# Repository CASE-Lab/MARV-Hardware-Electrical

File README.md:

# MARV-Hardware-Electrical
Contains the electrical design files fo the MARV system. These includes the PCBs and system wiring diagram and specific wire function diagram. Some of the PCB projects includes a component library, otherwise the CASE-Association case-eagle-libraries have been used, found here: https://github.com/CASE-Association/case-eagle-libraries.git

This project uses both Eagle and KiCad ECAD programs. This is shown by folder names.

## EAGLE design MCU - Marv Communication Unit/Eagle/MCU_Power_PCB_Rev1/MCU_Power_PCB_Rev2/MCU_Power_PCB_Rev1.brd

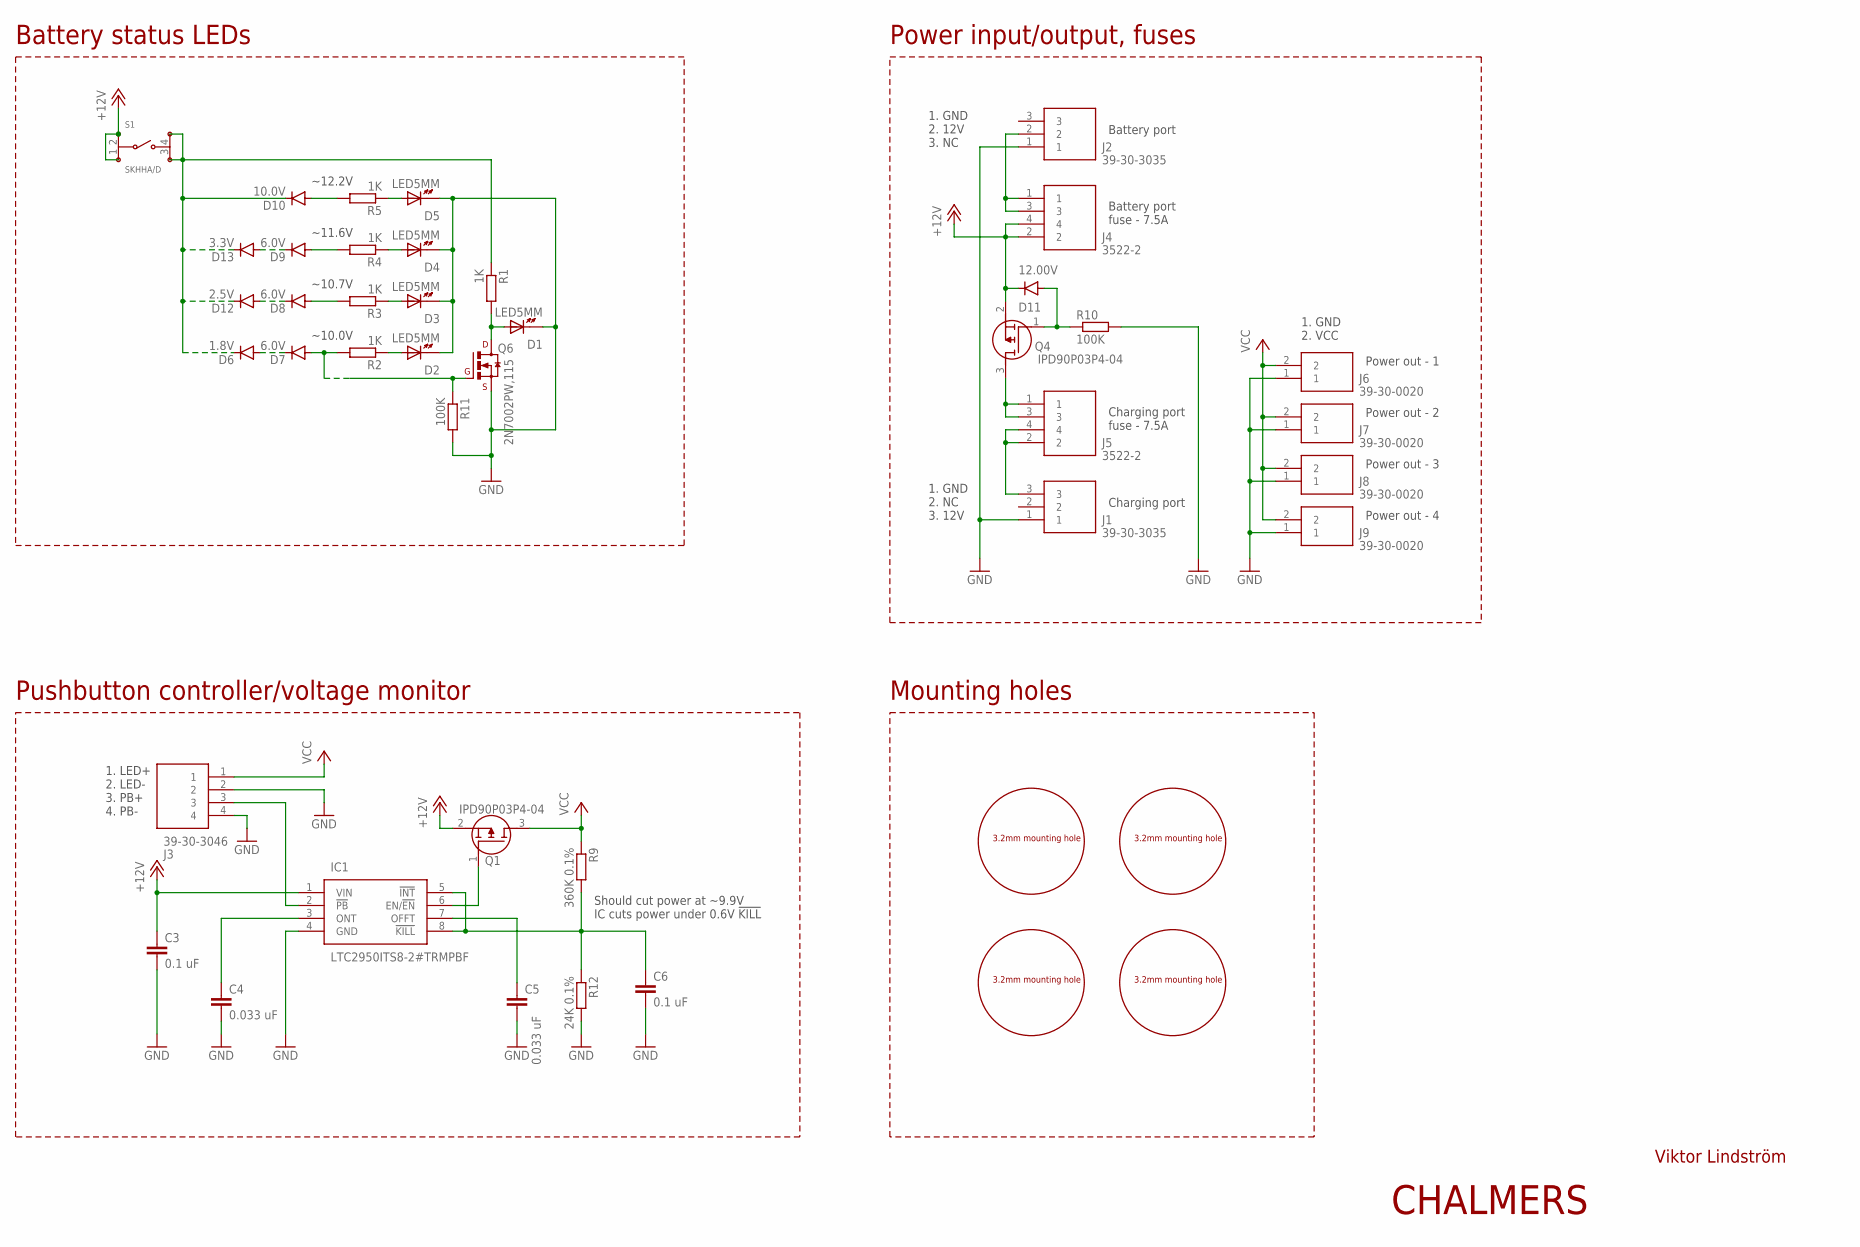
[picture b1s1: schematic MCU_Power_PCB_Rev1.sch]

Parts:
C3, C6: 0.1 uF; C0603
C4, C5: 0.033 uF; C0603
D1, D2, D3, D4, D5: LED5MM
D6: 1.8V; SOD-123_MINI-SMA
D7, D8, D9: 6.0V; SOD-123_MINI-SMA
D10: 10.0V; SOD-123_MINI-SMA
D11: 12.00V; SOD-123_MINI-SMA
D12: 2.5V; SOD-123_MINI-SMA
D13: 3.3V; SOD-123_MINI-SMA
HOLE1, HOLE2, HOLE3, HOLE4: M3_MOUNTING_HOLE
IC1: LTC2950ITS8-2#TRMPBF; SOT65P280X100-8N
J1, J2: 39-30-3035; 39303035
J3: 39-30-3046; 39303046
J4, J5: 3522-2; 35222
J6, J7, J8, J9: 39-30-0020; 39-30-1020_1
Q1, Q4: IPD90P03P4-04; PG-TO252-3-11
Q6: 2N7002PW,115; SOT323
R1, R2, R3, R4, R5: 1K; R0603
R9: 360K 0.1%; R0603
R10, R11: 100K; R0603
R12: 24K 0.1%; R0603
S1: SKHHA/D

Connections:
+12V: C3.1, D11.C, IC1.1 (VIN), J4.2, J4.4, Q1.2 (S), Q4.2 (S), S1.1, S1.2
GND: C3.2, C4.2, C5.2, C6.2, D1.K, D2.K, D3.K, D4.K, D5.K, IC1.4 (GND), J1.1, J2.1, J3.2, J3.4, J6.1, J7.1, J8.1, J9.1, Q6.2 (S), R10.2, R11.2, R12.2
unnamed: J5.1, J5.3, Q4.3 (D)
unnamed: C4.1, IC1.3 (ONT)
unnamed: D2.A, R2.1
unnamed: D7.A, Q6.1 (G), R2.2, R11.1
unnamed: D8.A, R3.2
unnamed: D9.A, R4.2
unnamed: D10.A, R5.2
unnamed: D3.A, R3.1
unnamed: D4.A, R4.1
unnamed: D5.A, R5.1
unnamed: IC1.2 (!PB), J3.3
unnamed: D1.A, Q6.3 (D), R1.2
unnamed: J2.2, J4.1, J4.3
unnamed: D6.A, D7.C
unnamed: D6.C, D10.C, D12.C, D13.C, R1.1, S1.3, S1.4
unnamed: C5.1, IC1.7 (OFFT)
unnamed: J1.3, J5.2, J5.4
unnamed: D8.C, D12.A
unnamed: D11.A, Q4.1 (G), R10.1
unnamed: D9.C, D13.A
unnamed: C6.1, IC1.5 (!INT), IC1.8 (!KILL), R9.2, R12.1
unnamed: IC1.6 (EN/!EN), Q1.1 (G)
VCC: J3.1, J6.2, J7.2, J8.2, J9.2, Q1.3 (D), R9.1

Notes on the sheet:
Charging port
Battery port
Power out - 4
Power out - 3
Power out - 2
Power out - 1
Battery port fuse - 7.5A
Should cut power at ~9.9V IC cuts power under 0.6V !KILL
1. LED+ 2. LED- 3. PB+ 4. PB-
Charging port fuse - 7.5A
1. GND 2. 12V 3. NC
1. GND 2. NC 3. 12V
1. GND 2. VCC
Battery status LEDs
Power input/output, fuses
Pushbutton controller/voltage monitor
Mounting holes
Viktor Lindström
CHALMERS
~12.2V
~11.6V
~10.0V
~10.7V

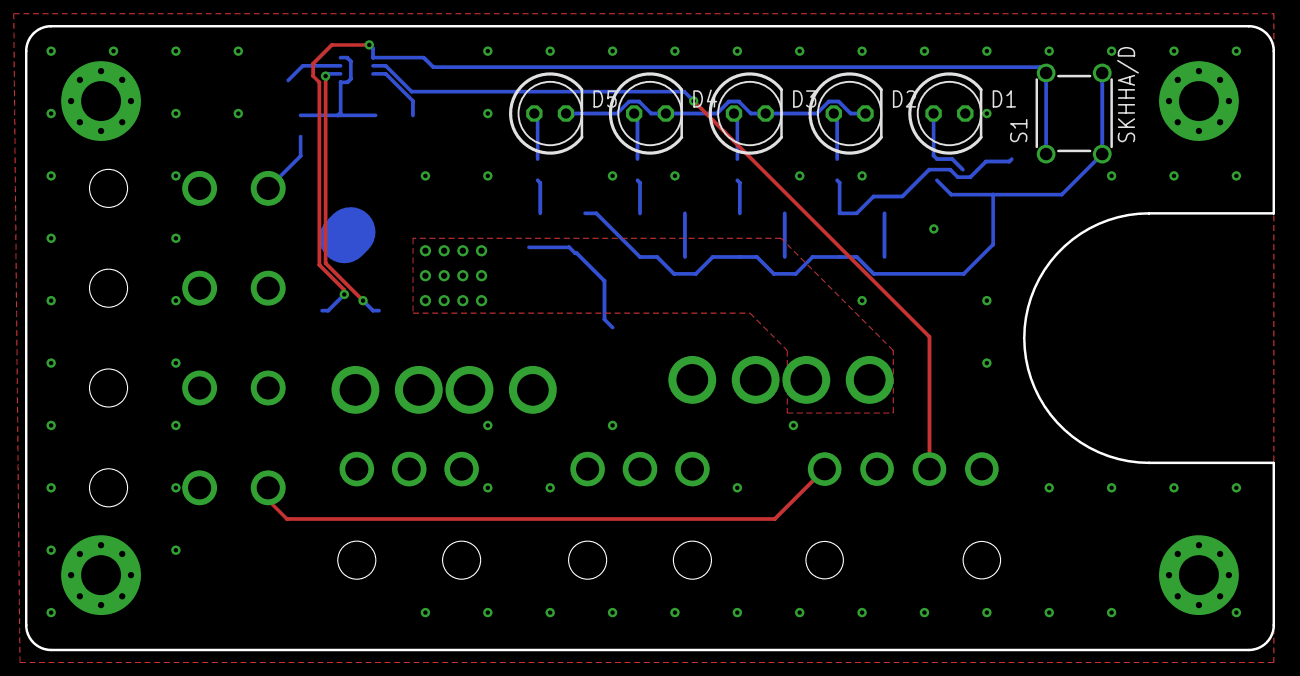
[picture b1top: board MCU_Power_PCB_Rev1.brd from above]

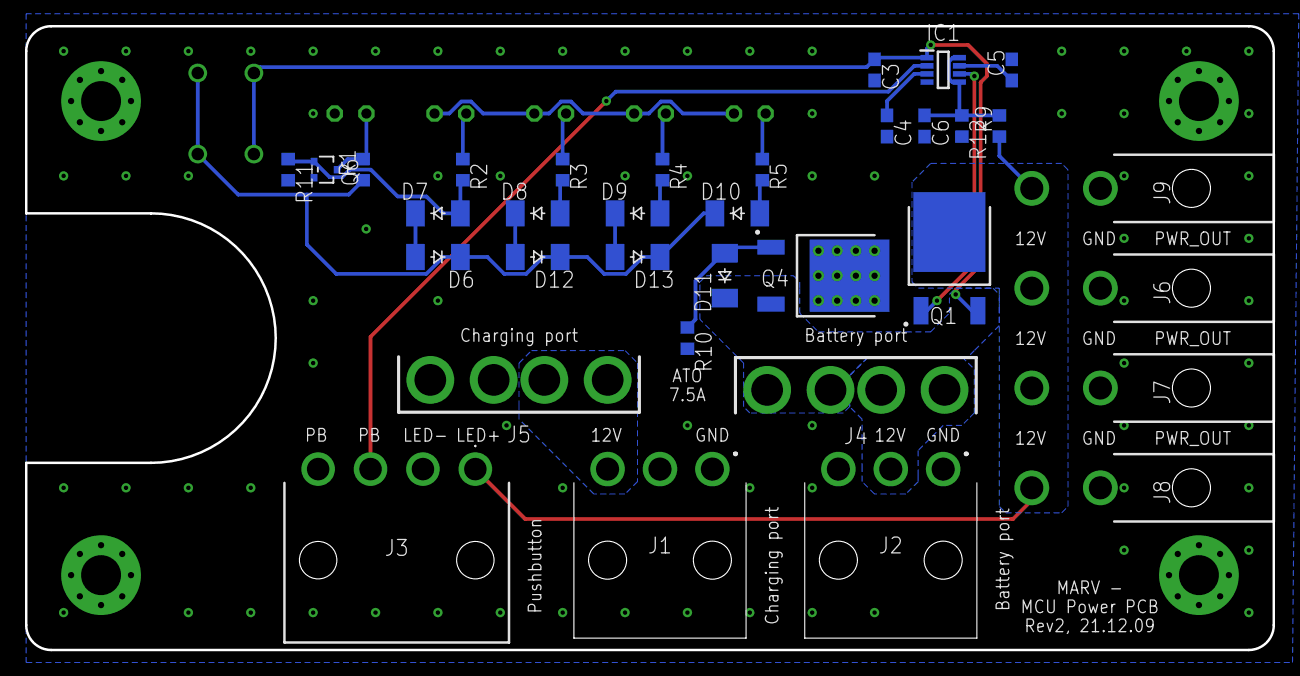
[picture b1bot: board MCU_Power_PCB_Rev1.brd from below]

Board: 2 copper layers, 100.0 x 50.0 mm, 44 parts (34 on the bottom side), 25 nets.

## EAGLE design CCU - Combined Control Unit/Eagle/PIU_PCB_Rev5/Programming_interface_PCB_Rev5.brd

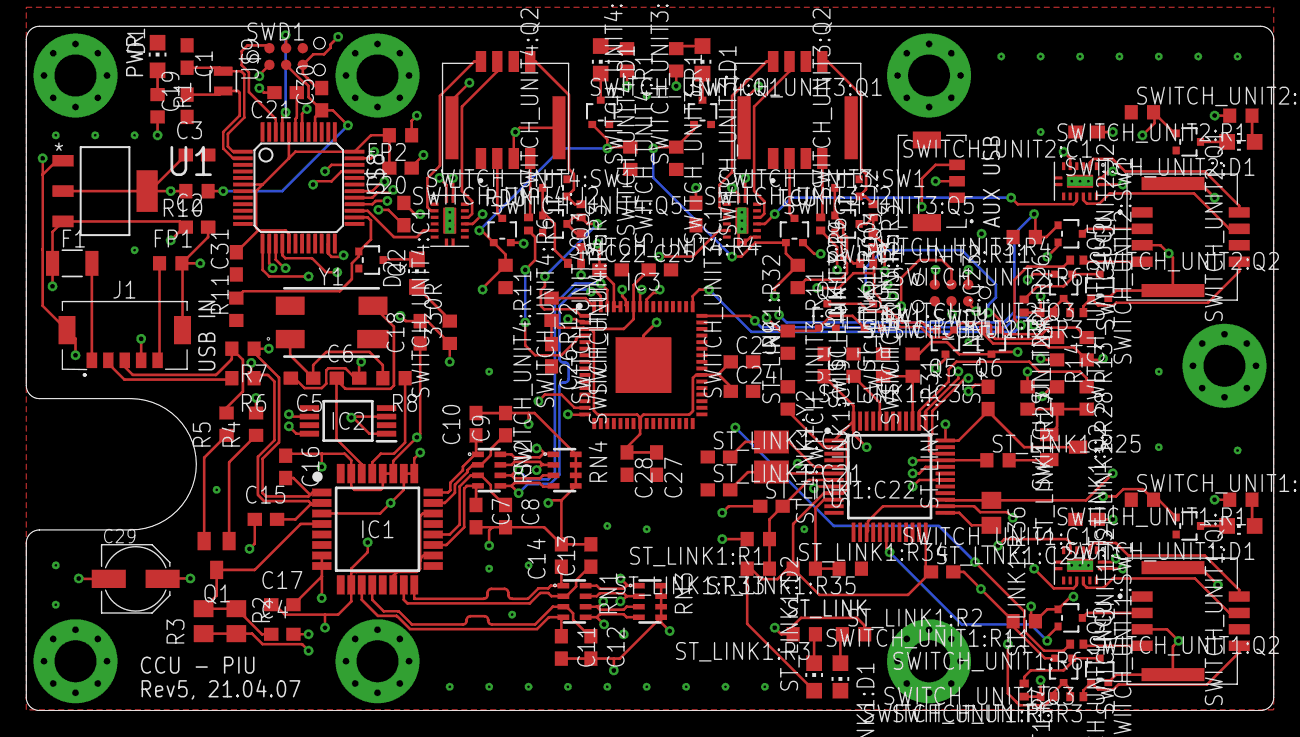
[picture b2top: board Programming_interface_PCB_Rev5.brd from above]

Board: 4 copper layers, 95.0 x 52.1 mm, 165 parts (0 on the bottom side), 117 nets.

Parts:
330R: 1K1; R0603
C1, C19: 4Pf?; C0603
C2, C4, C17, C18, C20, C24, C25, C26, C28, C30, C31: 0.1uF; C0603
C3: 10uF; C0603
C5, C6: 33pF; C0603
C7, C8, C9, C10, C11, C12, C13, C14, C15, C16: 22pF; C0603
C21, C22, C23, C27: 1uF; C0603
C29: 100uF; PANASONIC_C
D1, D2: CHIP-LED0805
F1: OZCJ0050; OZCJ
FP1, FP2: R0603
IC1: TUSB2046IBVFR; QFP80P900X900X160-32N
IC2: SN75240PW; SOP65P640X120-8N
IC3: CP2108-B03-GM; QFN50P900X900X90-65N
J1: 505568-0571; 5055680571
J2: 505567-0371; 5055680371
Q1: BC817; SOT23
Q2, Q3, Q4: 2N7002PW,115; SOT323
Q5, Q6: BSS223PW; SOT323
R1: 1K6; R0603
R2: 22; R0805
R3: 1K5; R0805
R4: 15K; R0603
R5, R8: 1K5; R0603
R6, R7: 27; R0603
R9, R12: 100K; R0603
R10, R11, R13, R14: 10K; R0603
RN1, RN2: CAY16-27R0F4LF; CAY16-J4
RN3, RN4: CAY16-1502F4LF; CAY16-J4
ST_LINK1:C19, ST_LINK1:C22, ST_LINK1:C23, ST_LINK1:C24: 0.1uF; C0603
ST_LINK1:C20, ST_LINK1:C21: 10pF; C0603
ST_LINK1:D1, ST_LINK1:D2: CHIP-LED0805
ST_LINK1:IC3: STM32F103CBT6TR; QFP50P900X900X160-48N
ST_LINK1:Q2: BC817; SOT23
ST_LINK1:R1: 0; R0603
ST_LINK1:R2, ST_LINK1:R3: 330; R0603
ST_LINK1:R25: 1K5; R0603
ST_LINK1:R26, ST_LINK1:R32: 10K; R0603
ST_LINK1:R27: 36K; R0603
ST_LINK1:R28: 100; R0603
ST_LINK1:R29, ST_LINK1:R33: 100K; R0603
ST_LINK1:R30, ST_LINK1:R34, ST_LINK1:R35: 4K7; R0603
ST_LINK1:R31: 2K7; R0603
ST_LINK1:R36: 100; R0805
ST_LINK1:SWD1: SWD_TAGCONNECTNO-LEG; TC2030-IDC-NL
ST_LINK1:Y2: NX3225GD-8MHZ-STD-CRA-3; RESC3226X100N
SWD1: SWD_TAGCONNECTNO-LEG; TC2030-IDC-NL
SWITCH_UNIT1:C1, SWITCH_UNIT2:C1, SWITCH_UNIT3:C1, SWITCH_UNIT4:C1: 0.1uF; C0603
SWITCH_UNIT1:D1, SWITCH_UNIT2:D1, SWITCH_UNIT3:D1, SWITCH_UNIT4:D1: CHIP-LED0805
SWITCH_UNIT1:J2, SWITCH_UNIT2:J2, SWITCH_UNIT3:J2, SWITCH_UNIT4:J2: 505433-0871; 5054330871
SWITCH_UNIT1:Q1, SWITCH_UNIT1:Q2, SWITCH_UNIT1:Q3, SWITCH_UNIT1:Q5, SWITCH_UNIT2:Q1, SWITCH_UNIT2:Q2, SWITCH_UNIT2:Q3, SWITCH_UNIT2:Q5, SWITCH_UNIT3:Q1, SWITCH_UNIT3:Q2, SWITCH_UNIT3:Q3, SWITCH_UNIT3:Q5, SWITCH_UNIT4:Q1, SWITCH_UNIT4:Q2, SWITCH_UNIT4:Q3, SWITCH_UNIT4:Q5: 2N7002PW,115; SOT323
SWITCH_UNIT1:R1, SWITCH_UNIT2:R1, SWITCH_UNIT3:R1, SWITCH_UNIT4:R1: 1K6; R0603
SWITCH_UNIT1:R2, SWITCH_UNIT2:R2, SWITCH_UNIT3:R2, SWITCH_UNIT4:R2: -; R0603
SWITCH_UNIT1:R3, SWITCH_UNIT2:R3, SWITCH_UNIT3:R3, SWITCH_UNIT4:R3: -; R0402
SWITCH_UNIT1:R4, SWITCH_UNIT1:R5, SWITCH_UNIT2:R4, SWITCH_UNIT2:R5, SWITCH_UNIT3:R4, SWITCH_UNIT3:R5, SWITCH_UNIT4:R4, SWITCH_UNIT4:R5: 1K; R0402
SWITCH_UNIT1:R6, SWITCH_UNIT2:R6, SWITCH_UNIT3:R6, SWITCH_UNIT4:R6: 0R; R0402
SWITCH_UNIT1:R11, SWITCH_UNIT2:R11, SWITCH_UNIT3:R11, SWITCH_UNIT4:R11: 10K; R0603
SWITCH_UNIT1:SW1, SWITCH_UNIT2:SW1, SWITCH_UNIT3:SW1, SWITCH_UNIT4:SW1: TMUX1309QBQBRQ1; QFN16-4X4
U1: LD1117S33TR; SOT230P700X180-4N
U$1, U$2, U$3, U$4, U$5, U$6, U$7: M3_MOUNTING_HOLE
U$8: SAMD21G18A-ARDUINO; TQFP48
U$9: ST2012SB32768H5KPWAA
Y1: ABMM-6.000MHZ-B2-T

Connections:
+3V3: 330R.1, C3.1, C17.1, C18.2, FP2.1, IC1.3, IC1.10, IC1.14, IC1.18, IC1.22, IC1.25, IC1.26, Q5.2, R2.2, R3.1, R10.2, R14.2, SWD1.1, SWITCH_UNIT1:R4.2, SWITCH_UNIT1:R5.2, SWITCH_UNIT2:R4.2, SWITCH_UNIT2:R5.2, SWITCH_UNIT3:R4.2, SWITCH_UNIT3:R5.2, SWITCH_UNIT4:R4.2, SWITCH_UNIT4:R5.2, U1.2, U1.4
+5V: C2.1, C22.1, C29.+, F1.1, IC3.60, IC3.61, Q6.2, R1.2, R4.2, R13.2, SWITCH_UNIT1:C1.1, SWITCH_UNIT1:R1.2, SWITCH_UNIT1:SW1.16, SWITCH_UNIT2:C1.1, SWITCH_UNIT2:R1.2, SWITCH_UNIT2:SW1.16, SWITCH_UNIT3:C1.1, SWITCH_UNIT3:R1.2, SWITCH_UNIT3:SW1.16, SWITCH_UNIT4:C1.1, SWITCH_UNIT4:R1.2, SWITCH_UNIT4:SW1.16, U1.3
D1_2_N: C11.1, IC1.11, RN1.7
D1_2_P: C12.1, IC1.12, RN1.5
D1_N: RN1.8, RN3.7, ST_LINK1:IC3.32
D1_P: RN1.6, RN3.5, ST_LINK1:IC3.33, ST_LINK1:R25.1
D2_2_N: C13.1, IC1.15, RN1.3
D2_2_P: C14.1, IC1.16, RN1.1
D2_N: RN1.4, RN3.3, U$8.33
D2_P: RN1.2, RN3.1, U$8.34
D3_2_N: C7.1, IC1.19, RN2.7
D3_2_P: C8.1, IC1.20, RN2.5
D3_N: IC3.63, RN2.8, RN4.7
D3_P: IC3.62, RN2.6, RN4.5
D4_2_N: C9.1, IC1.23, RN2.3
D4_2_P: C10.1, IC1.24, RN2.1
D4_N: J2.3, RN2.4, RN4.3
D4_P: J2.2, RN2.2, RN4.1
GND: C1.1, C2.2, C3.2, C4.2, C5.2, C6.2, C7.2, C8.2, C9.2, C10.2, C11.2, C12.2, C13.2, C14.2, C15.1, C16.1, C17.2, C18.1, C19.1, C20.1, C21.2, C22.2, C23.2, C24.2, C25.2, C26.2, C27.2, C28.2, C29.-, C30.2, C31.1, D1.C, FP1.2, IC1.7, IC1.8, IC1.27, IC1.28, IC1.31, IC2.1, IC2.3, IC3.2, IC3.25, IC3.59, IC3.65, J1.4, J1.MP1, J1.MP2, J2.1, J2.MP1, J2.MP2, Q2.2, Q3.2, Q4.2, R9.1, R11.1, RN3.2, RN3.4, RN3.6, RN3.8, RN4.2, RN4.4, RN4.6, RN4.8, ST_LINK1:C19.1, ST_LINK1:C20.1, ST_LINK1:C21.1, ST_LINK1:C22.1, ST_LINK1:C23.2, ST_LINK1:C24.2, ST_LINK1:D1.C, ST_LINK1:IC3.8, ST_LINK1:IC3.20, ST_LINK1:IC3.23, ST_LINK1:IC3.35, ST_LINK1:IC3.47, ST_LINK1:R27.1, ST_LINK1:R29.2, ST_LINK1:R30.2, ST_LINK1:R32.2, ST_LINK1:R35.1, ST_LINK1:SWD1.5, SWD1.5, SWITCH_UNIT1:C1.2, SWITCH_UNIT1:J2.5, SWITCH_UNIT1:J2.MP1, SWITCH_UNIT1:J2.MP2, SWITCH_UNIT1:Q1.2, SWITCH_UNIT1:Q2.2, SWITCH_UNIT1:Q3.2, SWITCH_UNIT1:R2.1, SWITCH_UNIT1:R11.2, SWITCH_UNIT1:SW1.8, SWITCH_UNIT1:SW1.9, SWITCH_UNIT1:SW1.10, SWITCH_UNIT1:SW1.EXP, SWITCH_UNIT1:SW1.P$1, SWITCH_UNIT1:SW1.P$2, SWITCH_UNIT1:SW1.P$3, SWITCH_UNIT2:C1.2, SWITCH_UNIT2:J2.5, SWITCH_UNIT2:J2.MP1, SWITCH_UNIT2:J2.MP2, SWITCH_UNIT2:Q1.2, SWITCH_UNIT2:Q2.2, SWITCH_UNIT2:Q3.2, SWITCH_UNIT2:R2.1, SWITCH_UNIT2:R11.2, SWITCH_UNIT2:SW1.8, SWITCH_UNIT2:SW1.9, SWITCH_UNIT2:SW1.10, SWITCH_UNIT2:SW1.EXP, SWITCH_UNIT2:SW1.P$1, SWITCH_UNIT2:SW1.P$2, SWITCH_UNIT2:SW1.P$3, SWITCH_UNIT3:C1.2, SWITCH_UNIT3:J2.5, SWITCH_UNIT3:J2.MP1, SWITCH_UNIT3:J2.MP2, SWITCH_UNIT3:Q1.2, SWITCH_UNIT3:Q2.2, SWITCH_UNIT3:Q3.2, SWITCH_UNIT3:R2.1, SWITCH_UNIT3:R11.2, SWITCH_UNIT3:SW1.8, SWITCH_UNIT3:SW1.9, SWITCH_UNIT3:SW1.10, SWITCH_UNIT3:SW1.EXP, SWITCH_UNIT3:SW1.P$1, SWITCH_UNIT3:SW1.P$2, SWITCH_UNIT3:SW1.P$3, SWITCH_UNIT4:C1.2, SWITCH_UNIT4:J2.5, SWITCH_UNIT4:J2.MP1, SWITCH_UNIT4:J2.MP2, SWITCH_UNIT4:Q1.2, SWITCH_UNIT4:Q2.2, SWITCH_UNIT4:Q3.2, SWITCH_UNIT4:R2.1, SWITCH_UNIT4:R11.2, SWITCH_UNIT4:SW1.8, SWITCH_UNIT4:SW1.9, SWITCH_UNIT4:SW1.10, SWITCH_UNIT4:SW1.EXP, SWITCH_UNIT4:SW1.P$1, SWITCH_UNIT4:SW1.P$2, SWITCH_UNIT4:SW1.P$3, U1.1, U$8.5, U$8.18, U$8.35, U$8.42
unnamed: C4.1, IC1.4, Q1.3, R2.1, R3.2
unnamed: FP1.1, J1.5
unnamed: Q1.1, R4.1
unnamed: Q1.2, R5.1
unnamed: Q4.3, Q5.1, R14.1
unnamed: Q3.3, Q6.1, R13.1
unnamed: D1.A, R1.1
unnamed: C20.2, C31.2, FP2.2, U$8.6, U$8.17, U$8.36, U$8.44
unnamed: C1.2, U$8.1, U$9.P$2
unnamed: IC1.29, R8.1
unnamed: C6.1, IC1.30, Y1.3
unnamed: C5.1, R8.2, Y1.1
unnamed: C19.2, U$8.2, U$9.P$1
unnamed: SWD1.2, U$8.46
unnamed: C30.1, R10.1, SWD1.3, U$8.40
unnamed: SWD1.4, U$8.45
unnamed: C21.1, U$8.43
unnamed: 330R.2, D2.A
unnamed: IC3.64, R12.1
unnamed: D2.C, Q2.3
unnamed: Q6.3, ST_LINK1:R26.2, ST_LINK1:R31.1
unnamed: Q2.1, R11.2, U$8.26
unnamed: Q5.3, ST_LINK1:C19.2, ST_LINK1:C23.1, ST_LINK1:C24.1, ST_LINK1:D2.A, ST_LINK1:IC3.1, ST_LINK1:IC3.9, ST_LINK1:IC3.24, ST_LINK1:IC3.36, ST_LINK1:IC3.48, ST_LINK1:Q2.3, ST_LINK1:R33.2, ST_LINK1:R34.1, ST_LINK1:SWD1.1
unnamed: F1.2, J1.1
NCU_NRST_ON: SWITCH_UNIT1:Q1.1, SWITCH_UNIT1:Q5.1, SWITCH_UNIT1:R2.2, SWITCH_UNIT1:R11.1, U$8.14
NCU_ON: SWITCH_UNIT1:SW1.6, U$8.30
PDU_NRST_ON: SWITCH_UNIT4:Q1.1, SWITCH_UNIT4:Q5.1, SWITCH_UNIT4:R2.2, SWITCH_UNIT4:R11.1, U$8.23
PDU_ON: SWITCH_UNIT4:SW1.6, U$8.27
RX_NCU: IC3.56, SWITCH_UNIT1:Q3.3, SWITCH_UNIT1:R3.2, SWITCH_UNIT1:R5.1
RX_PDU: IC3.1, SWITCH_UNIT4:Q3.3, SWITCH_UNIT4:R3.2, SWITCH_UNIT4:R5.1
RX_TCU: IC3.15, SWITCH_UNIT3:Q3.3, SWITCH_UNIT3:R3.2, SWITCH_UNIT3:R5.1
RX_UCU: IC3.48, SWITCH_UNIT2:Q3.3, SWITCH_UNIT2:R3.2, SWITCH_UNIT2:R5.1
ST_LINK1:N$1: ST_LINK1:D1.A, ST_LINK1:R2.1
ST_LINK1:N$3: ST_LINK1:D2.C, ST_LINK1:R3.1
ST_LINK1:N$7: ST_LINK1:Q2.2, ST_LINK1:R25.2
ST_LINK1:N$8: ST_LINK1:Q2.1, ST_LINK1:R26.1, ST_LINK1:R27.2, ST_LINK1:R28.2
ST_LINK1:N$15: ST_LINK1:IC3.39, ST_LINK1:R30.1, ST_LINK1:R31.2
ST_LINK1:N$16: ST_LINK1:IC3.2, ST_LINK1:R32.1
ST_LINK1:N$21: ST_LINK1:IC3.44, ST_LINK1:R29.1
ST_LINK1:N$22: ST_LINK1:C20.2, ST_LINK1:IC3.5, ST_LINK1:Y2.1
ST_LINK1:N$23: ST_LINK1:IC3.10, ST_LINK1:R34.2, ST_LINK1:R35.2
ST_LINK1:N$24: ST_LINK1:C21.2, ST_LINK1:IC3.6, ST_LINK1:Y2.2
ST_LINK1:N$25: ST_LINK1:C22.2, ST_LINK1:IC3.7, ST_LINK1:R1.1, ST_LINK1:R33.1
ST_LINK1:N$26: ST_LINK1:IC3.25, ST_LINK1:R36.2
ST_LINK1:STLK_LED: ST_LINK1:IC3.30, ST_LINK1:R2.2, ST_LINK1:R3.2
ST_LINK1:STM_NRST: ST_LINK1:R1.2, ST_LINK1:SWD1.3
ST_LINK1:STM_SWCLK: ST_LINK1:IC3.37, ST_LINK1:SWD1.4
ST_LINK1:STM_SWDIO: ST_LINK1:IC3.34, ST_LINK1:SWD1.2
ST_LINK1:USB_RENUM: ST_LINK1:IC3.38, ST_LINK1:R28.1
ST_LINK_EN: Q3.1, Q4.1, R9.2, U$8.13
ST_LINK_NRST_OUT: ST_LINK1:IC3.18, SWITCH_UNIT1:Q5.2, SWITCH_UNIT2:Q5.2, SWITCH_UNIT3:Q5.2, SWITCH_UNIT4:Q5.2
ST_LINK_SWDCLK_OUT: ST_LINK1:IC3.15, ST_LINK1:IC3.26, SWITCH_UNIT1:SW1.12, SWITCH_UNIT2:SW1.12, SWITCH_UNIT3:SW1.12, SWITCH_UNIT4:SW1.12
ST_LINK_SWDIO_OUT: ST_LINK1:IC3.27, ST_LINK1:R36.1, SWITCH_UNIT1:SW1.1, SWITCH_UNIT2:SW1.1, SWITCH_UNIT3:SW1.1, SWITCH_UNIT4:SW1.1
SWITCH_UNIT1:N$2: SWITCH_UNIT1:D1.C, SWITCH_UNIT1:Q1.3
SWITCH_UNIT1:N$3: SWITCH_UNIT1:D1.A, SWITCH_UNIT1:R1.1
SWITCH_UNIT1:N$4: SWITCH_UNIT1:Q2.3, SWITCH_UNIT1:Q3.1, SWITCH_UNIT1:R4.1
SWITCH_UNIT1:RX_STM32: SWITCH_UNIT1:J2.7, SWITCH_UNIT1:R6.1
SWITCH_UNIT1:TX_STM32: SWITCH_UNIT1:J2.8, SWITCH_UNIT1:Q2.1, SWITCH_UNIT1:R3.1
SWITCH_UNIT1:UNIT_NRST: SWITCH_UNIT1:J2.3, SWITCH_UNIT1:Q5.3
SWITCH_UNIT1:UNIT_SWCLK: SWITCH_UNIT1:J2.4, SWITCH_UNIT1:SW1.13
SWITCH_UNIT1:UNIT_SWDIO: SWITCH_UNIT1:J2.2, SWITCH_UNIT1:SW1.3
SWITCH_UNIT2:N$2: SWITCH_UNIT2:D1.C, SWITCH_UNIT2:Q1.3
SWITCH_UNIT2:N$3: SWITCH_UNIT2:D1.A, SWITCH_UNIT2:R1.1
SWITCH_UNIT2:N$4: SWITCH_UNIT2:Q2.3, SWITCH_UNIT2:Q3.1, SWITCH_UNIT2:R4.1
SWITCH_UNIT2:RX_STM32: SWITCH_UNIT2:J2.7, SWITCH_UNIT2:R6.1
SWITCH_UNIT2:TX_STM32: SWITCH_UNIT2:J2.8, SWITCH_UNIT2:Q2.1, SWITCH_UNIT2:R3.1
SWITCH_UNIT2:UNIT_NRST: SWITCH_UNIT2:J2.3, SWITCH_UNIT2:Q5.3
SWITCH_UNIT2:UNIT_SWCLK: SWITCH_UNIT2:J2.4, SWITCH_UNIT2:SW1.13
SWITCH_UNIT2:UNIT_SWDIO: SWITCH_UNIT2:J2.2, SWITCH_UNIT2:SW1.3
SWITCH_UNIT3:N$2: SWITCH_UNIT3:D1.C, SWITCH_UNIT3:Q1.3
SWITCH_UNIT3:N$3: SWITCH_UNIT3:D1.A, SWITCH_UNIT3:R1.1
SWITCH_UNIT3:N$4: SWITCH_UNIT3:Q2.3, SWITCH_UNIT3:Q3.1, SWITCH_UNIT3:R4.1
SWITCH_UNIT3:RX_STM32: SWITCH_UNIT3:J2.7, SWITCH_UNIT3:R6.1
SWITCH_UNIT3:TX_STM32: SWITCH_UNIT3:J2.8, SWITCH_UNIT3:Q2.1, SWITCH_UNIT3:R3.1
SWITCH_UNIT3:UNIT_NRST: SWITCH_UNIT3:J2.3, SWITCH_UNIT3:Q5.3
SWITCH_UNIT3:UNIT_SWCLK: SWITCH_UNIT3:J2.4, SWITCH_UNIT3:SW1.13
SWITCH_UNIT3:UNIT_SWDIO: SWITCH_UNIT3:J2.2, SWITCH_UNIT3:SW1.3
SWITCH_UNIT4:N$2: SWITCH_UNIT4:D1.C, SWITCH_UNIT4:Q1.3
SWITCH_UNIT4:N$3: SWITCH_UNIT4:D1.A, SWITCH_UNIT4:R1.1
SWITCH_UNIT4:N$4: SWITCH_UNIT4:Q2.3, SWITCH_UNIT4:Q3.1, SWITCH_UNIT4:R4.1
SWITCH_UNIT4:RX_STM32: SWITCH_UNIT4:J2.7, SWITCH_UNIT4:R6.1
SWITCH_UNIT4:TX_STM32: SWITCH_UNIT4:J2.8, SWITCH_UNIT4:Q2.1, SWITCH_UNIT4:R3.1
SWITCH_UNIT4:UNIT_NRST: SWITCH_UNIT4:J2.3, SWITCH_UNIT4:Q5.3
SWITCH_UNIT4:UNIT_SWCLK: SWITCH_UNIT4:J2.4, SWITCH_UNIT4:SW1.13
SWITCH_UNIT4:UNIT_SWDIO: SWITCH_UNIT4:J2.2, SWITCH_UNIT4:SW1.3
TCU_NRST_ON: SWITCH_UNIT3:Q1.1, SWITCH_UNIT3:Q5.1, SWITCH_UNIT3:R2.2, SWITCH_UNIT3:R11.1, U$8.16
TCU_ON: SWITCH_UNIT3:SW1.6, U$8.28
TX_NCU: IC3.57, SWITCH_UNIT1:R6.2
TX_PDU: IC3.4, SWITCH_UNIT4:R6.2
TX_TCU: IC3.16, SWITCH_UNIT3:R6.2
TX_UCU: IC3.49, SWITCH_UNIT2:R6.2
UCU_NRST_ON: SWITCH_UNIT2:Q1.1, SWITCH_UNIT2:Q5.1, SWITCH_UNIT2:R2.2, SWITCH_UNIT2:R11.1, U$8.15
UCU_ON: SWITCH_UNIT2:SW1.6, U$8.29
USB_D1_N: C15.2, IC1.2, IC2.8, R6.1
USB_D1_P: C16.2, IC1.1, IC2.6, R7.1
USB_D2_N: J1.2, R6.2
USB_D2_P: J1.3, R5.2, R7.2
VIO: C23.1, C24.1, C25.1, C26.1, C27.1, C28.1, IC3.3, IC3.24, IC3.39, IC3.58, R12.2

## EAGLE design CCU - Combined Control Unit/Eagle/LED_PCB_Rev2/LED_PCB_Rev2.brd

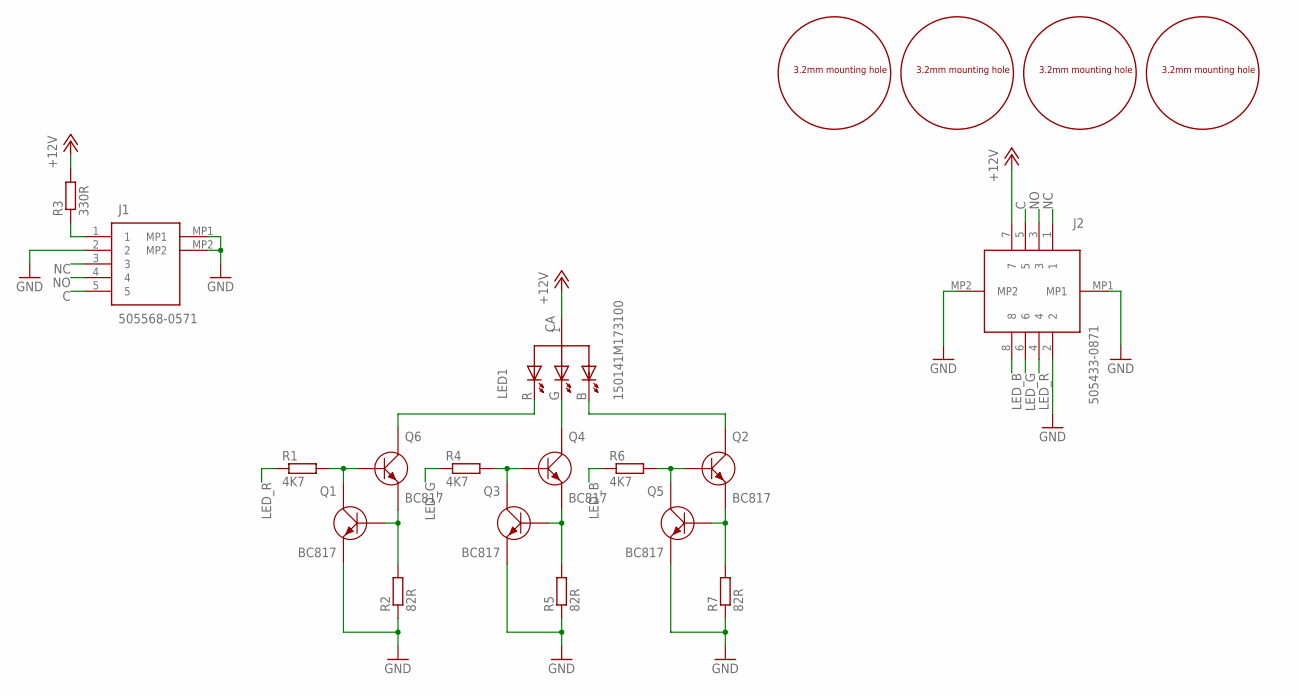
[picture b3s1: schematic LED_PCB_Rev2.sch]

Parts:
J1: 505568-0571; 5055680571
J2: 505433-0871; 5054330871
LED1: 150141M173100
Q1, Q2, Q3, Q4, Q5, Q6: BC817; SOT23
R1, R4, R6: 4K7; R0603
R2, R5, R7: 82R; R0603
R3: 330R; R0603
U$1, U$2, U$3, U$4: M3_MOUNTING_HOLE

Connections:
+12V: J2.7, LED1.1 (CA), R3.2
C: J1.5, J2.5
GND: J1.2, J1.MP1, J1.MP2, J2.2, J2.MP1, J2.MP2, Q1.2 (E), Q3.2 (E), Q5.2 (E), R2.1, R5.1, R7.1
LED_B: J2.8, R6.1
LED_G: J2.6, R4.1
LED_R: J2.4, R1.1
unnamed: Q1.1 (B), Q6.2 (E), R2.2
unnamed: Q1.3 (C), Q6.1 (B), R1.2
unnamed: LED1.4 (G), Q4.3 (C)
unnamed: Q3.1 (B), Q4.2 (E), R5.2
unnamed: Q3.3 (C), Q4.1 (B), R4.2
unnamed: LED1.3 (R), Q6.3 (C)
unnamed: Q2.2 (E), Q5.1 (B), R7.2
unnamed: Q2.1 (B), Q5.3 (C), R6.2
unnamed: LED1.2 (B), Q2.3 (C)
unnamed: J1.1, R3.1
NC: J1.3, J2.1
NO: J1.4, J2.3

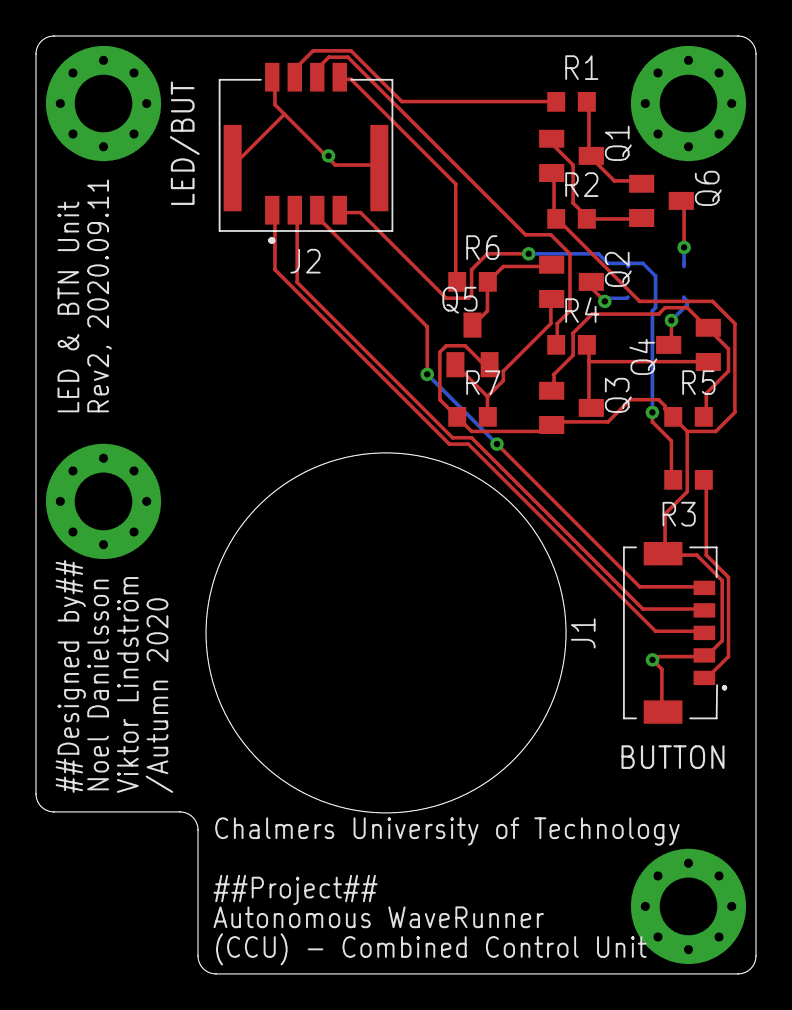
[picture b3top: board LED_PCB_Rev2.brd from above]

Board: 2 copper layers, 40.0 x 52.1 mm, 20 parts (1 on the bottom side), 18 nets.

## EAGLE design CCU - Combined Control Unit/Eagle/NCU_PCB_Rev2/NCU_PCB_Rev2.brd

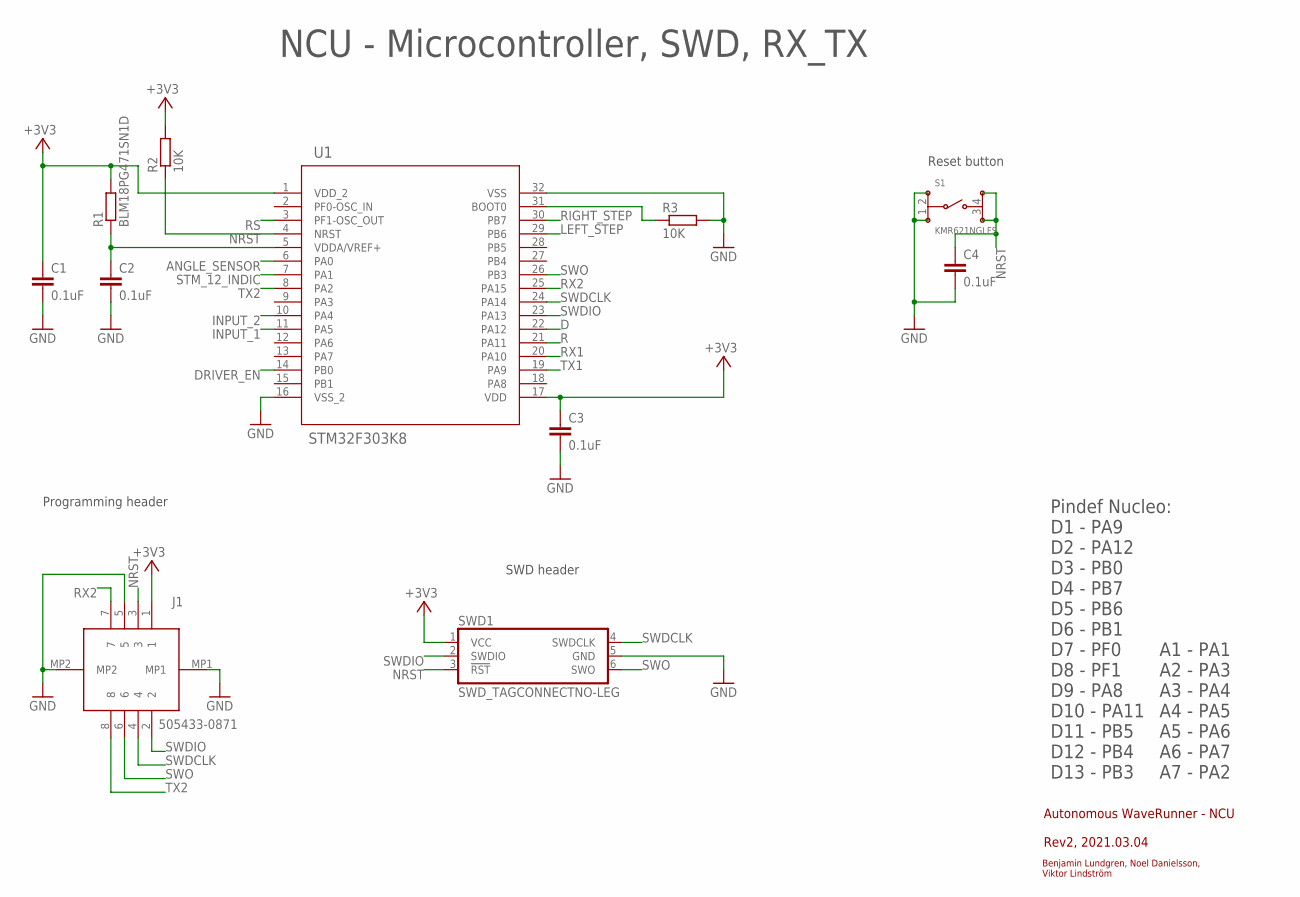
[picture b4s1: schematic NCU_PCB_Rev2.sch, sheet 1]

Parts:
C1, C2, C3, C4: 0.1uF; C0603
J1: 505433-0871; 5054330871
R1: BLM18PG471SN1D; R0603
R2, R3: 10K; R0603
S1: KMR621NGLFS
SWD1: SWD_TAGCONNECTNO-LEG; TC2030-IDC-NL
U1: STM32F303K8; LQFP-32

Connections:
+3V3: C1.1, C3.1, J1.1, R1.2, R2.2, SWD1.1 (VCC), U1.1 (VDD_2), U1.17 (VDD); also elsewhere on the board
ANGLE_SENSOR: U1.6 (PA0); also elsewhere on the board
D: U1.22 (PA12); also elsewhere on the board
DRIVER_EN: U1.14 (PB0); also elsewhere on the board
GND: C1.2, C2.2, C3.2, C4.2, J1.5, J1.MP1, J1.MP2, R3.2, S1.1, S1.2, SWD1.5 (GND), U1.16 (VSS_2), U1.32 (VSS); also elsewhere on the board
INPUT_1: U1.11 (PA5); also elsewhere on the board
INPUT_2: U1.10 (PA4); also elsewhere on the board
LEFT_STEP: U1.29 (PB6); also elsewhere on the board
unnamed: C2.1, R1.1, U1.5 (VDDA/VREF+)
unnamed: R3.1, U1.31 (BOOT0)
NRST: C4.1, J1.3, R2.1, S1.3, S1.4, SWD1.3 (!RST), U1.4 (NRST)
R: U1.21 (PA11); also elsewhere on the board
RIGHT_STEP: U1.30 (PB7); also elsewhere on the board
RS: U1.3 (PF1-OSC_OUT); also elsewhere on the board
RX1: U1.20 (PA10); also elsewhere on the board
RX2: J1.7, U1.25 (PA15)
STM_12_INDIC: U1.7 (PA1); also elsewhere on the board
SWDCLK: J1.4, SWD1.4 (SWDCLK), U1.24 (PA14)
SWDIO: J1.2, SWD1.2 (SWDIO), U1.23 (PA13)
SWO: J1.6, SWD1.6 (SWO), U1.26 (PB3)
TX1: U1.19 (PA9); also elsewhere on the board
TX2: J1.8, U1.8 (PA2)

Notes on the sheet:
Autonomous WaveRunner - NCU
Rev2, 2021.03.04
Benjamin Lundgren, Noel Danielsson, Viktor Lindström
Pindef Nucleo: D1 - PA9 D2 - PA12 D3 - PB0 D4 - PB7 D5 - PB6 D6 - PB1 D7 - PF0 D8 - PF1 D9 - PA8 D10 - PA11 D11 - PB5 D12 - PB4 D13 - PB3
A1 - PA1 A2 - PA3 A3 - PA4 A4 - PA5 A5 - PA6 A6 - PA7 A7 - PA2
NCU - Microcontroller, SWD, RX_TX
Programming header
SWD header
Reset button

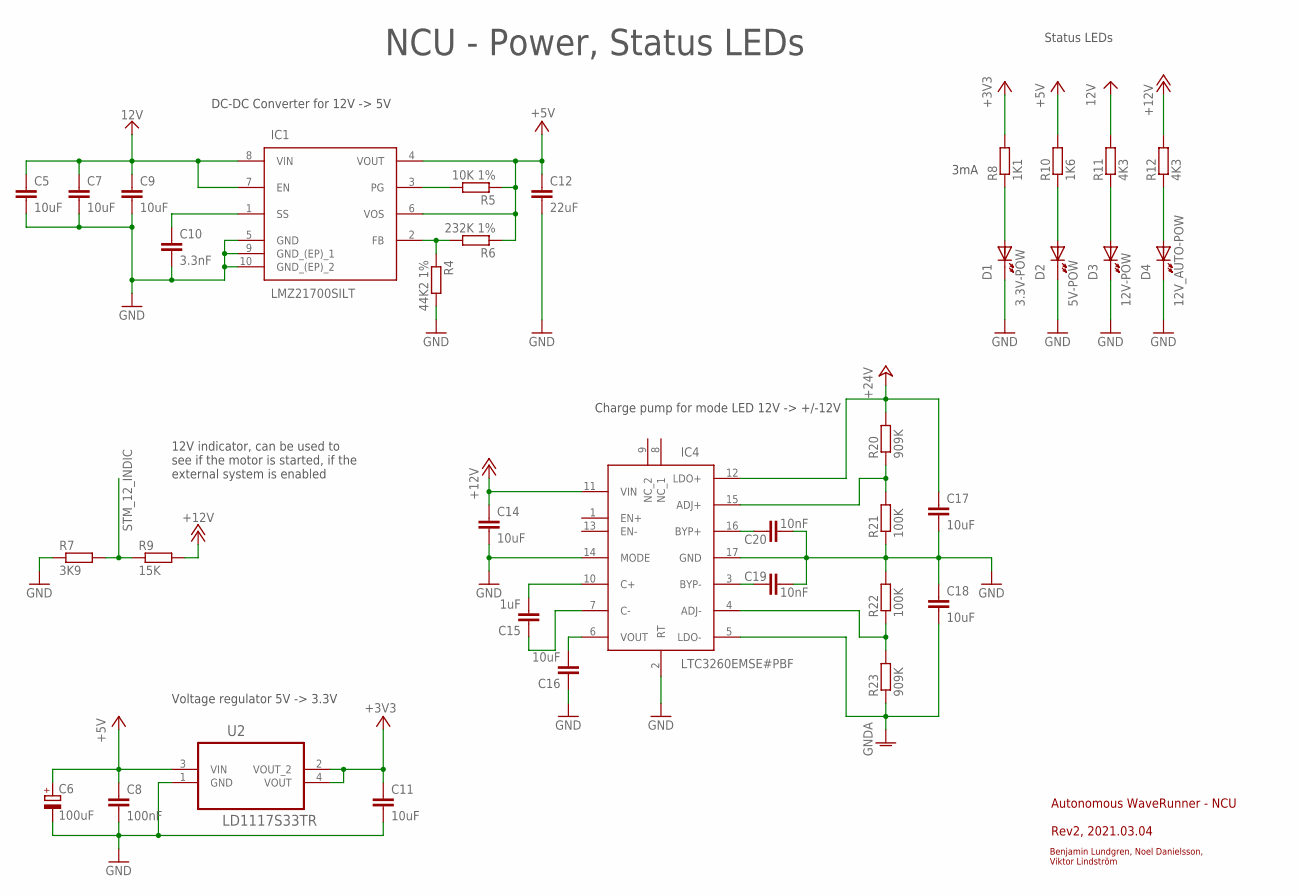
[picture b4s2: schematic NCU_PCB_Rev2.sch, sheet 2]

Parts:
C5, C7, C9, C14, C16, C17, C18: 10uF; C1206
C6: 100uF; PANASONIC_C
C8: 100nF; C0603
C10: 3.3nF; C0603
C11: 10uF; C0805
C12: 22uF; C0805
C15: 1uF; C0805
C19, C20: 10nF; C0603
D1: 3.3V-POW; CHIP-LED0805
D2: 5V-POW; CHIP-LED0805
D3: 12V-POW; CHIP-LED0805
D4: 12V_AUTO-POW; CHIP-LED0805
IC1: LMZ21700SILT; SIL0008E
IC4: LTC3260EMSE#PBF; SOP50P490X110-17N
R4: 44K2 1%; R0603
R5: 10K 1%; R0603
R6: 232K 1%; R0603
R7: 3K9; R0603
R8: 1K1; R0603
R9: 15K; R0603
R10: 1K6; R0603
R11, R12: 4K3; R0603
R20, R23: 909K; R0603
R21, R22: 100K; R0603
U2: LD1117S33TR; SOT230P700X180-4N

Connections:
12V: C5.1, C7.1, C9.1, IC1.7 (EN), IC1.8 (VIN), R11.2; also elsewhere on the board
+3V3: C11.1, R8.2, U2.2 (VOUT_2), U2.4 (VOUT); also elsewhere on the board
+5V: C6.+, C8.1, C12.1, IC1.4 (VOUT), IC1.6 (VOS), R5.1, R6.1, R10.2, U2.3 (VIN); also elsewhere on the board
+12V: C14.1, IC4.11 (VIN), R9.2, R12.2; also elsewhere on the board
+24V: C17.1, IC4.12 (LDO+), R20.2; also elsewhere on the board
GND: C5.2, C6.-, C7.2, C8.2, C9.2, C10.2, C11.2, C12.2, C14.2, C16.1, C17.2, C18.1, C19.2, C20.2, D1.C (K), D2.C (K), D3.C (K), D4.C (K), IC1.5 (GND), IC1.9 (GND_(EP)_1), IC1.10 (GND_(EP)_2), IC4.2 (RT), IC4.14 (MODE), IC4.17 (GND), R4.2, R7.1, R21.1, R22.2, U2.1 (GND); also elsewhere on the board
GNDA: C18.2, IC4.5 (LDO-), R23.1; also elsewhere on the board
unnamed: D4.A, R12.1
unnamed: IC1.2 (FB), R4.1, R6.2
unnamed: C10.1, IC1.1 (SS)
unnamed: C15.2, IC4.10 (C+)
unnamed: C15.1, IC4.7 (C-)
unnamed: C20.1, IC4.16 (BYP+)
unnamed: D3.A, R11.1
unnamed: IC1.3 (PG), R5.2
unnamed: C19.1, IC4.3 (BYP-)
unnamed: C16.2, IC4.6 (VOUT)
unnamed: IC4.15 (ADJ+), R20.1, R21.2
unnamed: IC4.4 (ADJ-), R22.1, R23.2
unnamed: D2.A, R10.1
unnamed: D1.A, R8.1
STM_12_INDIC: R7.2, R9.1; also elsewhere on the board

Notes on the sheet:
Autonomous WaveRunner - NCU
Rev2, 2021.03.04
Benjamin Lundgren, Noel Danielsson, Viktor Lindström
Status LEDs
NCU - Power, Status LEDs
Voltage regulator 5V -> 3.3V
DC-DC Converter for 12V -> 5V
12V indicator, can be used to see if the motor is started, if the external system is enabled
Charge pump for mode LED 12V -> +/-12V
3mA

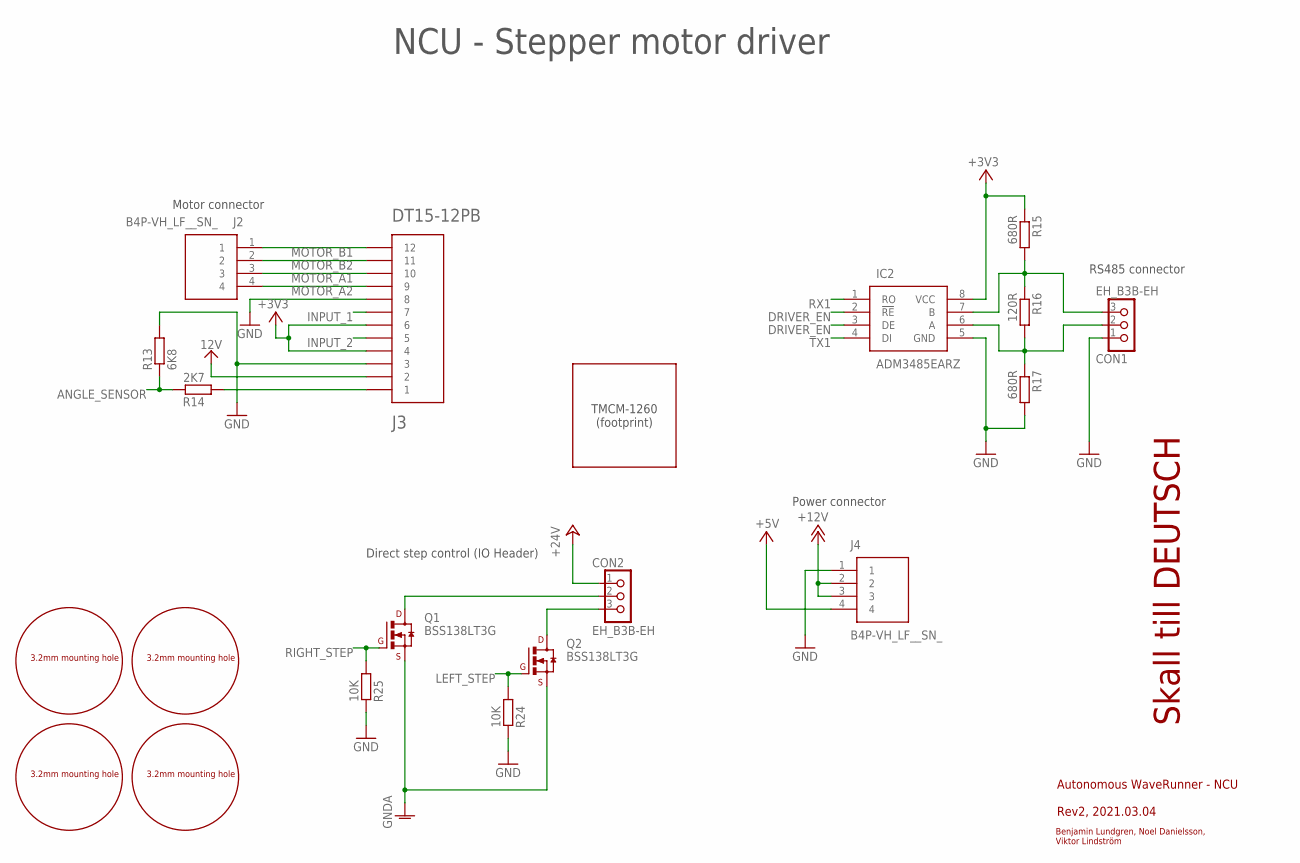
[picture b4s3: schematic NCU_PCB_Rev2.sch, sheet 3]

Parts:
CON1, CON2: EH_B3B-EH; B3B-EH
HOLE1, HOLE2, HOLE3, HOLE4: M3_MOUNTING_HOLE
IC2: ADM3485EARZ; SOIC127P600X175-8N
J2, J4: B4P-VH_LF__SN_; SHDR4W114P0X396_1X4_1578X850X9
J3: DT15-12PB; TE_DT15-12PB
MOD1: TMCM-1260; TMCM_1260
Q1, Q2: BSS138LT3G; SOT23
R13: 6K8; R0603
R14: 2K7; R0603
R15, R17: 680R; R0603
R16: 120R; R0603
R24, R25: 10K; R0603

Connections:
12V: J3.2; also elsewhere on the board
+3V3: IC2.8 (VCC), J3.4, J3.6, R15.1; also elsewhere on the board
+5V: J4.4; also elsewhere on the board
+12V: J4.2, J4.3; also elsewhere on the board
+24V: CON2.1; also elsewhere on the board
ANGLE_SENSOR: R13.1, R14.2; also elsewhere on the board
DRIVER_EN: IC2.2 (!RE), IC2.3 (DE); also elsewhere on the board
GND: CON1.1, IC2.5 (GND), J3.3, J3.8, J4.1, R13.2, R17.2, R24.2, R25.2; also elsewhere on the board
GNDA: Q1.2 (S), Q2.2 (S); also elsewhere on the board
INPUT_1: J3.7; also elsewhere on the board
INPUT_2: J3.5; also elsewhere on the board
LEFT_STEP: Q2.1 (G), R24.1; also elsewhere on the board
MOTOR_A1: J2.3, J3.10
MOTOR_A2: J2.4, J3.9
MOTOR_B1: J2.1, J3.12
MOTOR_B2: J2.2, J3.11
unnamed: CON1.3, IC2.7 (B), R15.2, R16.1
unnamed: J3.1, R14.1
unnamed: CON1.2, IC2.6 (A), R16.2, R17.1
unnamed: CON2.2, Q1.3 (D)
unnamed: CON2.3, Q2.3 (D)
RIGHT_STEP: Q1.1 (G), R25.1; also elsewhere on the board
RX1: IC2.1 (RO); also elsewhere on the board
TX1: IC2.4 (DI); also elsewhere on the board

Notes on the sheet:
Autonomous WaveRunner - NCU
Rev2, 2021.03.04
Benjamin Lundgren, Noel Danielsson, Viktor Lindström
NCU - Stepper motor driver
Skall till DEUTSCH
Power connector
Motor connector
RS485 connector
Direct step control (IO Header)

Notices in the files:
parts and their libraries:
CASE-Prog_Header: ©2009 ROFA.cz - modified and updated by Robert Darlington ‹rdarlington@gmail.com›
